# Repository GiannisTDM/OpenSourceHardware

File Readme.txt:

This project is intended to be a good base boost driver 
for the Laser hobbist community capable of supplying up to 1.4A.
By utilizing the files and/or information contained in them you agree to the following:

Shall not mass produce the driver and sell for a profit unless advising the head of the project
Giannis Koumoutsos/Giannis_TDM by emailing at giannislasershack@gmail.com so guidelines can be 
agreed upon.

Mass produce in this context means that a quantity of thirty (30) or more drivers were produced in a
run.

Said does not hold true if the individual is not selling them but produces said run for a project of
theirs. 

Thank you for reeding and enjoy the drivers!

Note: They are designed for manual assembly and testing

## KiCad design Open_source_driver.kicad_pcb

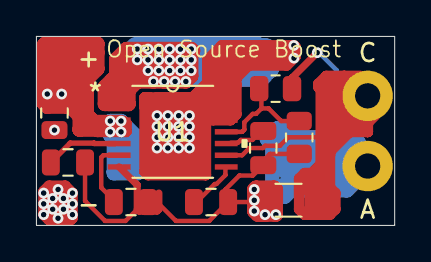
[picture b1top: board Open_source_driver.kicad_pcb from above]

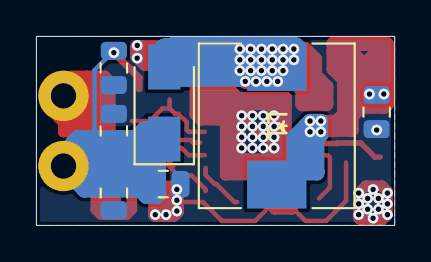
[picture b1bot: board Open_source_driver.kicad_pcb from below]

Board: 2 copper layers, 19.9 x 10.5 mm, 20 parts (7 on the bottom side), 10 nets.

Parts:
+: 1; MountingHole_2.7mm_Pad
-: 2; MountingHole_2.7mm_Pad
A: Output +/ Laser diode anode; MountingHole_2.7mm_Pad
C: Output -/ Laser diode cathode; MountingHole_2.7mm_Pad
C1: 10uF,16v 0805; C_0805_2012Metric
C2, C6, C7, C8, C9: 10uF, 16v 0805; C_0805_2012Metric
C3: 22uF, 0805, 6.3v; C_0805_2012Metric
C4: 1uF, 0805, 25v; C_0805_2012Metric
C5: 470nF, 0805,16v; C_0805_2012Metric
D1: B360AE-13; D_SMA
L1: 15uH; ETQ-P5M220YFK
R1: 120KΩ; R_0805_2012Metric
R2: 20k,0805; R_0805_2012Metric
R4: 100k, 0805; C_0805_2012Metric
R5: R_set; R_1206_3216Metric
U1: TPS61500; TPS61500PWP

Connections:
AGND: -.1, C1.2, C2.2, C3.2, C4.2, C5.2, C6.2, C7.2, C8.2, C9.2, R2.2, R4.2, R5.2, U1.7 (AGND), U1.12 (PGND), U1.13 (PGND), U1.14 (PGND)
FB: C.1, R5.1, U1.9 (FB)
unnamed: +.1, C1.1, C2.1, L1.1, U1.3 (vin), U1.4 (EN)
unnamed: C3.1, U1.5 (SS)
unnamed: C4.1, U1.6 (DIMC)
unnamed: C5.1, U1.8 (COMP)
unnamed: A.1, C6.1, C7.1, C8.1, C9.1, D1.1 (K), R1.1
unnamed: R1.2, R2.1, U1.11 (OVP)
unnamed: R4.1, U1.10 (FREQ)
SW: D1.2 (A), L1.2, U1.1 (sw), U1.2 (sw)

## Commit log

2023-06-29 Open source 3A buck mode laser/led driver
2023-06-29 1.4A capable boost mode laser/LED PSU

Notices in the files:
parts and their libraries:
Copyright 2021 Accelerated Designs. All rights reserved.
